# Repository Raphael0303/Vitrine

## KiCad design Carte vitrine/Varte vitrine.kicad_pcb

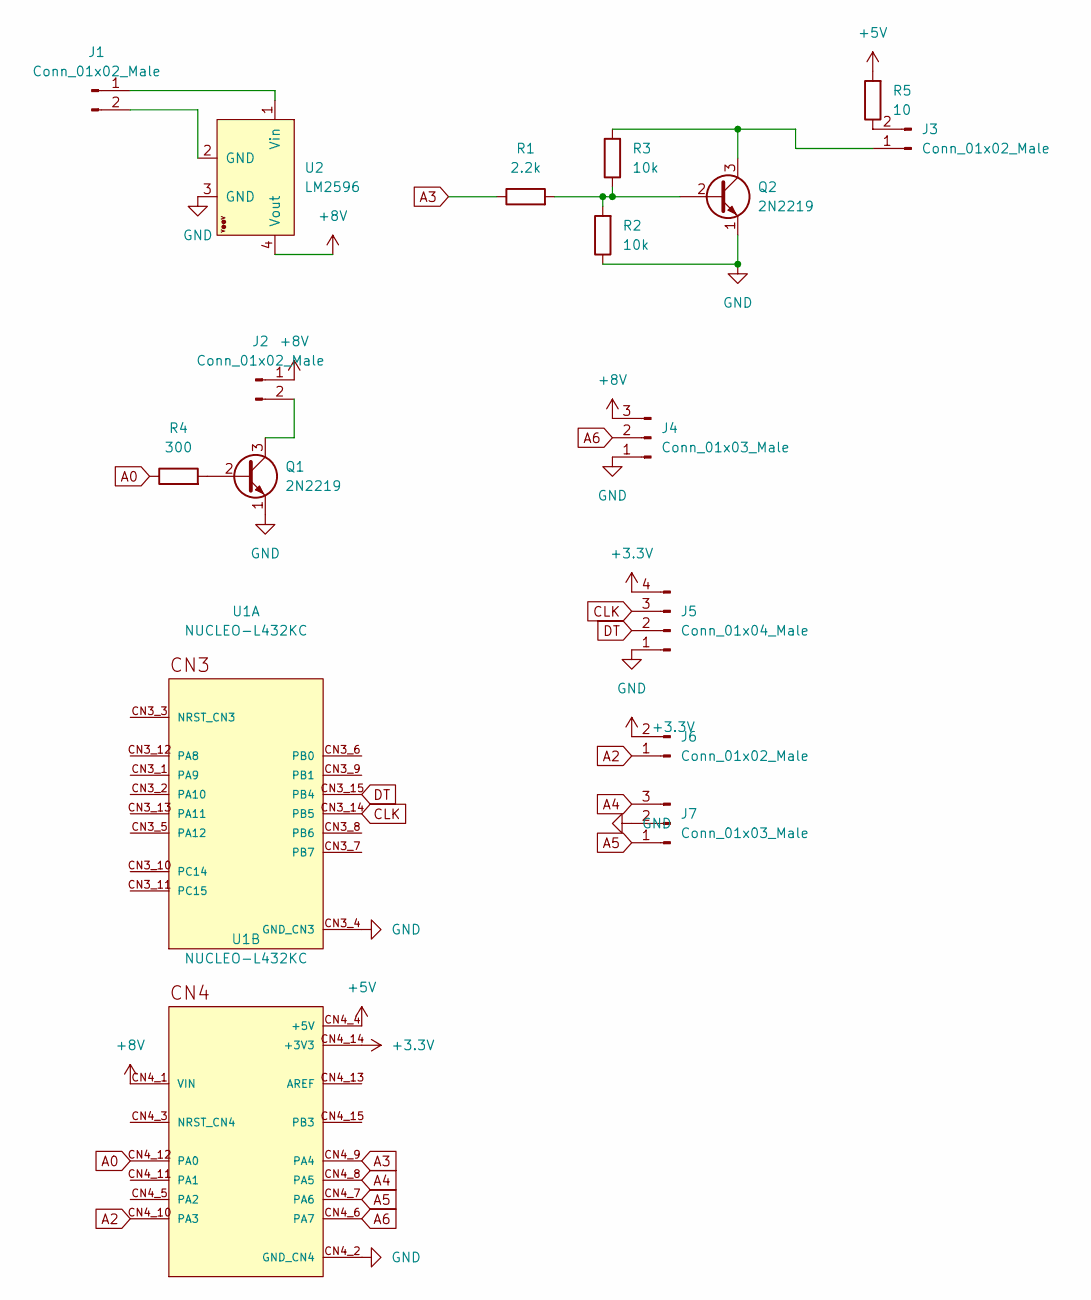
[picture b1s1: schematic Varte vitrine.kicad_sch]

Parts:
J1: Conn_01x02_Male; JST_VH_B2P-VH_1x02_P3.96mm_Vertical
J2, J3, J6: Conn_01x02_Male; JST_EH_B2B-EH-A_1x02_P2.50mm_Vertical
J4, J7: Conn_01x03_Male; JST_EH_B3B-EH-A_1x03_P2.50mm_Vertical
J5: Conn_01x04_Male; JST_EH_B4B-EH-A_1x04_P2.50mm_Vertical
Q1, Q2: 2N2219; TO-92L_Inline
R1: 2.2k; R_Axial_DIN0207_L6.3mm_D2.5mm_P15.24mm_Horizontal
R2, R3: 10k; R_Axial_DIN0207_L6.3mm_D2.5mm_P15.24mm_Horizontal
R4: 300; R_Axial_DIN0207_L6.3mm_D2.5mm_P15.24mm_Horizontal
R5: 10; R_Axial_DIN0207_L6.3mm_D2.5mm_P15.24mm_Horizontal
U1: NUCLEO-L432KC; MODULE_NUCLEO-L432KC; PARTREV N/A
U2: LM2596; YAAJ_DCDC_StepDown_LM2596

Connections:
+3V3: J5.4, J6.2, U1.CN4_14 (+3V3)
+5V: R5.2, U1.CN4_4 (+5V)
+8V: J2.1, J4.3, U1.CN4_1 (VIN), U2.4 (Vout)
A0: R4.1, U1.CN4_12 (PA0)
A2: J6.1, U1.CN4_10 (PA3)
A3: R1.1, U1.CN4_9 (PA4)
A4: J7.3, U1.CN4_8 (PA5)
A5: J7.1, U1.CN4_7 (PA6)
A6: J4.2, U1.CN4_6 (PA7)
CLK: J5.3, U1.CN3_14 (PB5)
DT: J5.2, U1.CN3_15 (PB4)
GND: J4.1, J5.1, J7.2, Q1.1 (E), Q2.1 (E), R2.1, U1.CN3_4 (GND_CN3), U1.CN4_2 (GND_CN4), U2.3 (GND)
unnamed: J1.1, U2.1 (Vin)
unnamed: J1.2, U2.2 (GND)
unnamed: J2.2, Q1.3 (C)
unnamed: J3.1, Q2.3 (C), R3.2
unnamed: J3.2, R5.1
unnamed: Q1.2 (B), R4.2
unnamed: Q2.2 (B), R1.2, R2.2, R3.1

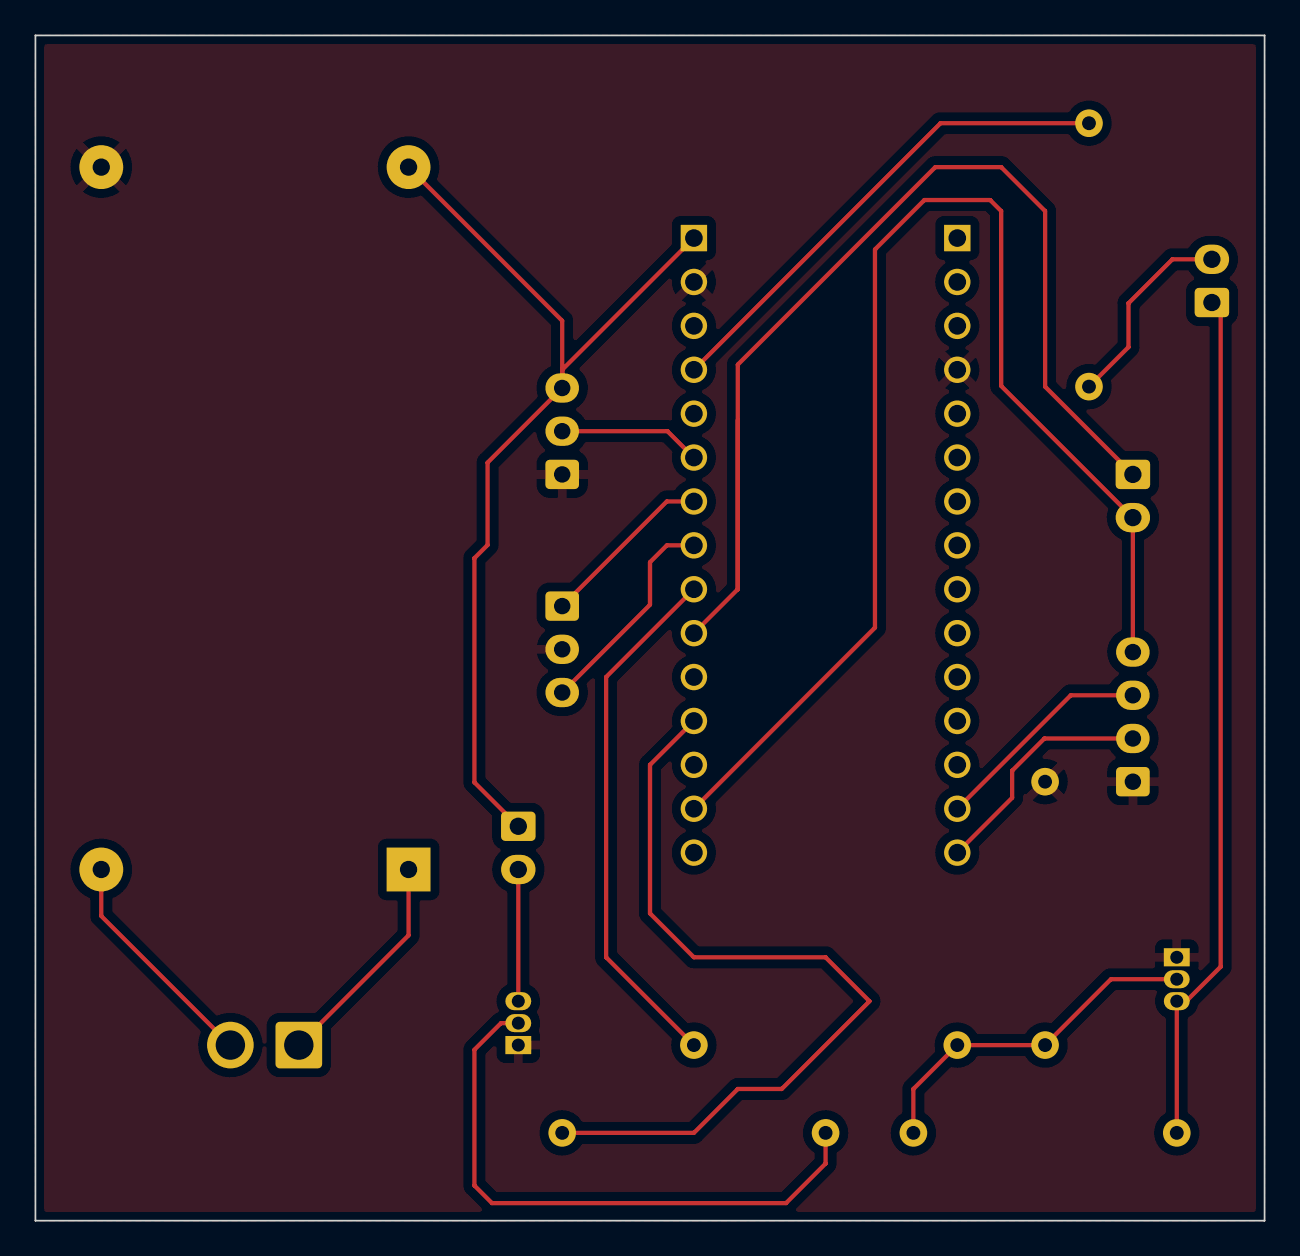
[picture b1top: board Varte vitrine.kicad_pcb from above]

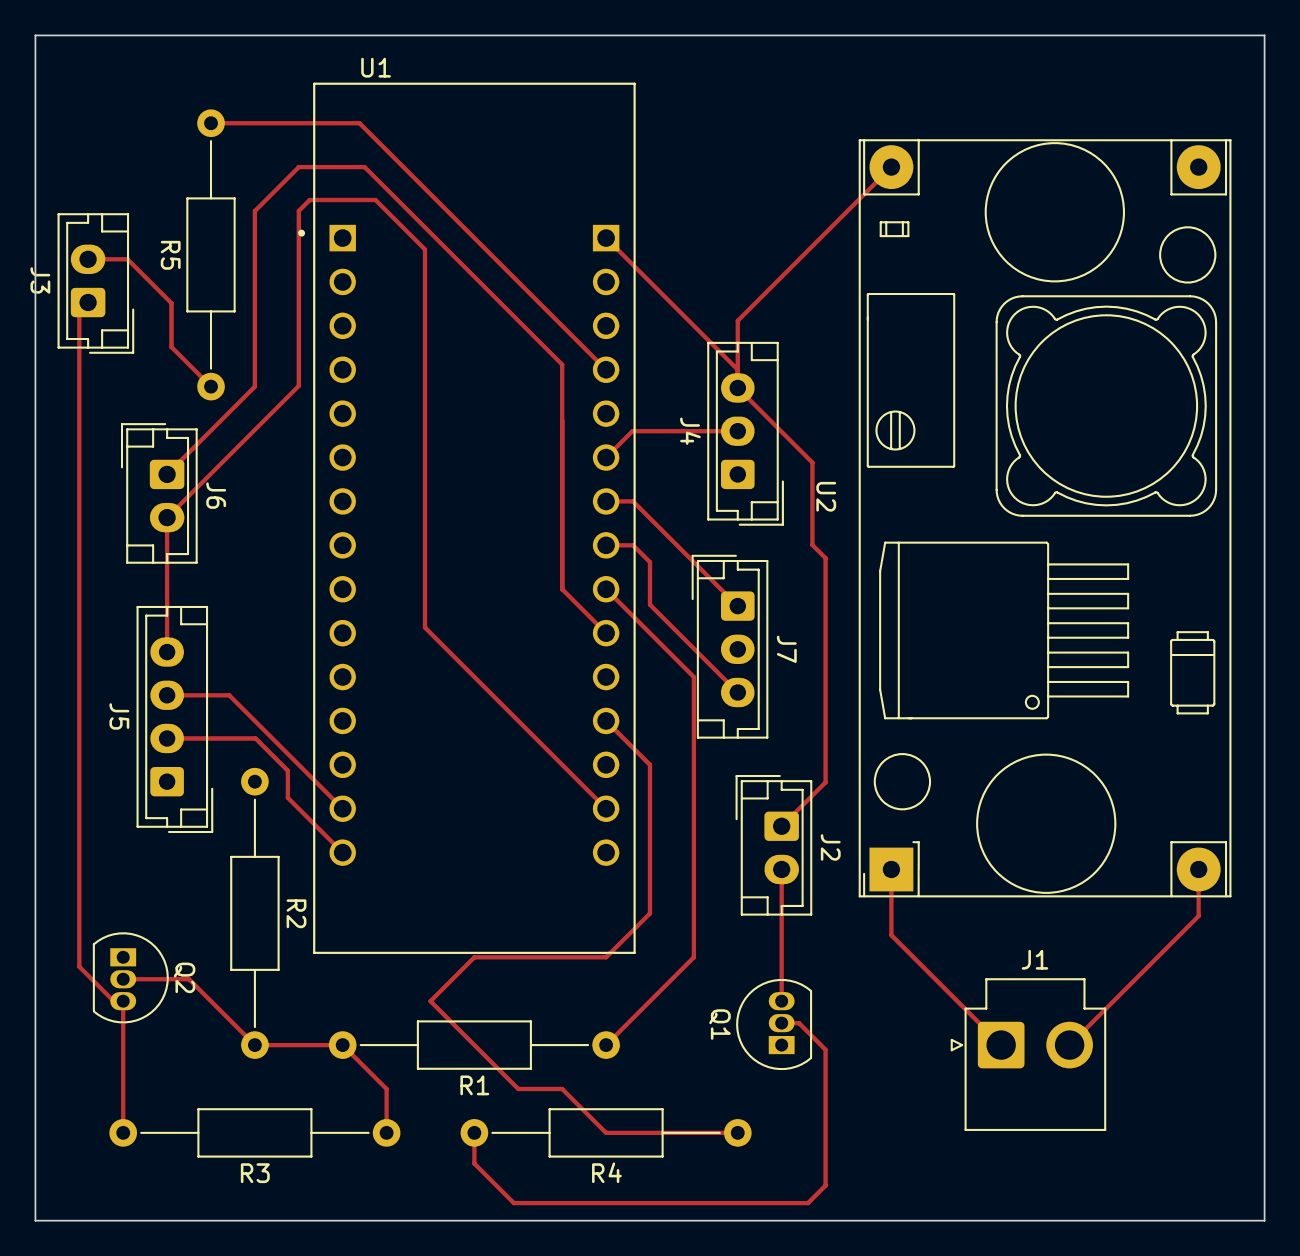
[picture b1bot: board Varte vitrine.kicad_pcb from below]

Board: 2 copper layers, 71.1 x 68.6 mm, 16 parts (16 on the bottom side), 19 nets.

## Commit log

2022-09-22 start
2022-09-22 fini
2022-09-22 Intégration code
